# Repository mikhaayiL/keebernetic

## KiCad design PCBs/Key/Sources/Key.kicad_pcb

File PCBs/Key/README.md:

# [keebernetic](../../README.md) : PCBs : key
Simple PCB for each switch \
Measures 14 mm x 18 mm \
Includes two routers (`In` and `Out`) for connecting the LED data pins

### BOM
- MX compatible switch
- 1N4148 sod-523
- SK6812 mini-E

### Preview

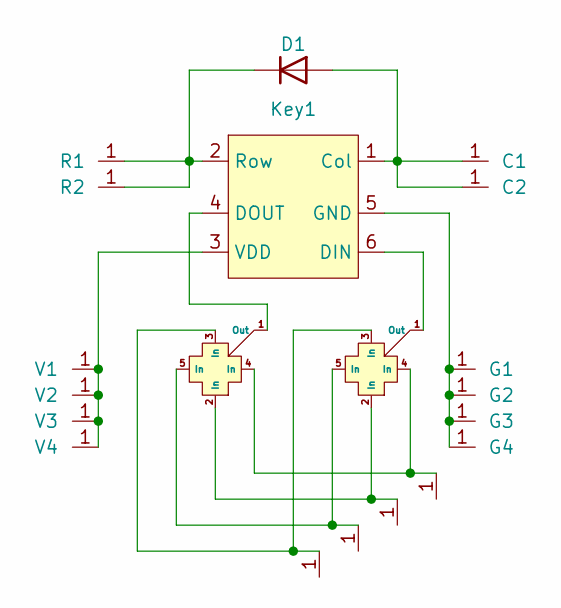
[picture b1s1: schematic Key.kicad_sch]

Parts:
C1, C2: Pad
D1: 1N4148WT; D_SOD-523
G1, G2, G3, G4: Pad
Key1: Key
P1, P2, P6, P7: Pad
R1, R2: Pad
RP1, RP2: Route_Pad
V1, V2, V3, V4: Pad

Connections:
unnamed: C1.1, C2.1, D1.2 (A), Key1.1 (Col)
unnamed: D1.1 (K), Key1.2 (Row), R1.1, R2.1
unnamed: Key1.6 (DIN), RP1.1 (Out)
unnamed: Key1.4 (DOUT), RP2.1 (Out)
unnamed: G1.1, G2.1, G3.1, G4.1, Key1.5 (GND)
unnamed: Key1.3 (VDD), V1.1, V2.1, V3.1, V4.1
unnamed: P1.1, RP1.4 (In), RP2.4 (In)
unnamed: P2.1, RP1.2 (In), RP2.2 (In)
unnamed: P6.1, RP1.3 (In), RP2.3 (In)
unnamed: P7.1, RP1.5 (In), RP2.5 (In)

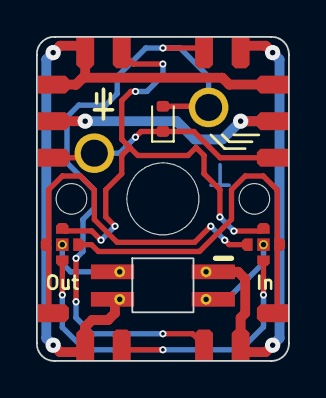
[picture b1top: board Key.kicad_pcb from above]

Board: 2 copper layers, 14.0 x 18.0 mm, 20 parts (0 on the bottom side), 10 nets.

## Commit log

2020-05-01 Added key for visual layouting
2020-05-02 Added parts of switch place build components
2020-05-02 Added parameterized concavity for column part
2020-05-04 Added column building logic
2020-05-05 Added main keyboard layout
2020-07-19 Added modules for building a bridge between columns and key switch borders
2020-07-24 Built borders of the main cluster
2020-07-31 Made a little refactoring
2020-08-02 Made another one refactoring
2020-08-08 Last commit before global reworking
2020-08-15 Added key for visual layouting with parts for sculpting layout
2020-08-16 Added modules to separate sculpting levels
2020-08-22 Added column building modules
2020-08-23 Added cluster layouts for left part of keyboard
2020-08-29 Corrected main cluster layout
2020-09-04 Deleted obsolete files
2020-10-09 Added case module
2020-10-10 Modules preparation for case creation
2023-12-10 Added PCB for the switch
